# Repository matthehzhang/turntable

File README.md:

# turntable
im building a vinyl record player from scratch

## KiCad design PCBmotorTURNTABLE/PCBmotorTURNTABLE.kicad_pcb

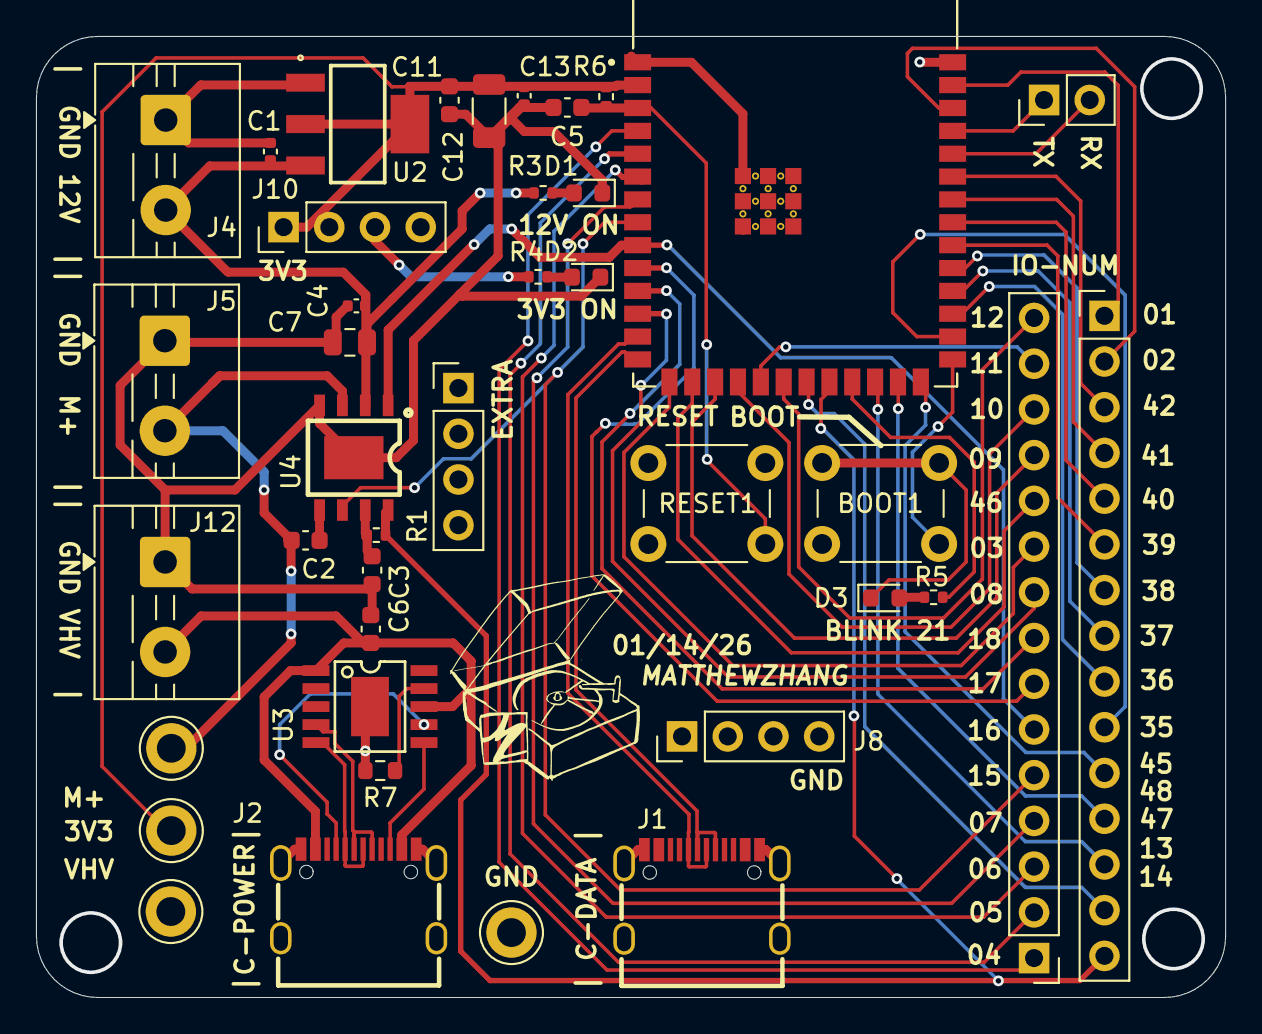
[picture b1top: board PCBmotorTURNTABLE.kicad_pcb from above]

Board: 2 copper layers, 66.1 x 53.4 mm, 40 parts (0 on the bottom side), 53 nets.

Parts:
3V3: TestPoint; TestPoint_Keystone_5010-5014_Multipurpose
BOOT1: SW_Push; SW_PUSH_6mm
C1: 100nf; C_0402_1005Metric
C2: 47nF; C_0603_1608Metric
C3, C6: 1uF; C_0603_1608Metric
C4: 0.1uF; C_0402_1005Metric
C5, C11: 10u; C_0603_1608Metric
C7: 10uF; C_0805_2012Metric
C12: 22u; C_1206_3216Metric
C13: 100n; C_0402_1005Metric
D1: RED; D_0603_1608Metric
D2, D3: GREEN; D_0603_1608Metric
EXTRA: Conn_01x04_Pin; PinHeader_1x04_P2.54mm_Vertical
GND: GND; TestPoint_Keystone_5010-5014_Multipurpose
J1, J2: USB_C_Receptacle_USB2.0_16P; USB-C_SMD-TYPE-C-31-M-12_1
J3, J6: Conn_01x15_Pin; PinHeader_1x15_P2.54mm_Vertical
J4, J5, J12: Screw_Terminal_01x02; TerminalBlock_MaiXu_MX126-5.0-02P_1x02_P5.00mm
J8, J10: Conn_01x04_Pin; PinHeader_1x04_P2.54mm_Vertical
J11: Conn_01x02_Pin; PinHeader_1x02_P2.54mm_Vertical
M+: M+; TestPoint_Keystone_5010-5014_Multipurpose
R1: 27K; R_0402_1005Metric
R3: 10k; R_0402_1005Metric
R4, R5: 1.2K; R_0402_1005Metric
R6: 10K; R_0402_1005Metric
R7: 24K; R_0603_1608Metric
RESET1: SW_Push; SW_PUSH_6mm
T2: VHV; TestPoint_Keystone_5010-5014_Multipurpose
U1: ESP32-S3-WROOM-1-N8; XCVR_ESP32-S3-WROOM-1-N8
U2: LD1117S33TR; LD11
U3: ch224a
U4: MP8040

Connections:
+3V3: 3V3.1, C11.1, C12.1, C13.1, J10.1, J10.2, J10.3, J10.4, R4.1, R6.1, U1.2 (3V3), U2.2 (OUT), U2.4 (OUT)
+12V: C1.1, C4.1, C7.1, J4.2, R3.1, U2.3 (IN), U4.2 (SP)
/M+: C2.2, J5.2, M+.1, U4.3 (SW)
/VHV: C6.1, J2.A4B9, J2.B4A9, J12.2, T2.1, U3.1 (VHV), U3.8 (VBUS)
D+: J1.A6 (D+), J1.B6 (D+), U1.14 (IO20)
D-: J1.A7 (D-), J1.B7 (D-), U1.13 (IO19)
DD+: J2.A6 (D+), J2.B6 (D+), U3.4 (DP)
DD-: J2.A7 (D-), J2.B7 (D-), U3.5 (DM)
ENABLE: C5.1, R6.2, RESET1.2, U1.3 (EN)
GND: BOOT1.1, C1.2, C3.2, C4.2, C5.2, C6.2, C7.2, C11.2, C12.2, C13.2, D1.1 (K), D2.1 (K), D3.1 (K), GND.1, J1.1, J1.4, J1.B1A12, J2.1, J2.4, J2.A1B12, J2.B1A12, J4.1, J5.1, J8.1, J8.2, J8.3, J8.4, J12.1, R7.1, RESET1.1, U1.1 (GND), U1.40 (GND), U1.41_1 (GND), U1.41_2 (GND), U1.41_3 (GND), U1.41_4 (GND), U1.41_5 (GND), U1.41_6 (GND), U1.41_7 (GND), U1.41_8 (GND), U1.41_9 (GND), U2.1 (GND), U3.11 (GND), U4.4 (GND), U4.9 (EP)
GPIO0: BOOT1.2, U1.27 (IO0)
GPIO1: J6.1, U1.39 (IO1)
GPIO2: J6.2, U1.38 (IO2)
GPIO3: J3.10, U1.15 (IO3)
GPIO4: J3.1, U1.4 (IO4)
GPIO5: J3.2, U1.5 (IO5)
GPIO6: J3.3, U1.6 (IO6)
GPIO7: J3.4, U1.7 (IO7)
GPIO8: J3.9, U1.12 (IO8)
GPIO9: J3.12, U1.17 (IO9)
GPIO10: J3.13, U1.18 (IO10)
GPIO11: J3.14, U1.19 (IO11)
GPIO12: J3.15, U1.20 (IO12)
GPIO13: J6.14, U1.21 (IO13)
GPIO14: J6.15, R1.1, U1.22 (IO14), U4.8 (FLT)
GPIO15: J3.5, U1.8 (IO15), U4.6 (SHDN)
GPIO16: J3.6, U1.9 (IO16), U4.1 (PWM)
GPIO17: J3.7, U1.10 (IO17)
GPIO18: J3.8, U1.11 (IO18)
GPIO21: R5.1, U1.23 (IO21)
GPIO35: J6.10, U1.28 (IO35)
GPIO36: J6.9, U1.29 (IO36)
GPIO37: J6.8, U1.30 (IO37)
GPIO38: J6.7, U1.31 (IO38)
GPIO39: J6.6, U1.32 (IO39)
GPIO40: J6.5, U1.33 (IO40)
GPIO41: J6.4, U1.34 (IO41)
GPIO42: J6.3, U1.35 (IO42)
GPIO45: J6.11, U1.26 (IO45)
GPIO46: J3.11, U1.16 (IO46)
GPIO47: J6.13, U1.24 (IO47)
GPIO48: J6.12, U1.25 (IO48)
unnamed: D1.2 (A), R3.2
unnamed: D2.2 (A), R4.2
unnamed: D3.2 (A), R5.2
unnamed: J2.A5 (CC1), U3.7 (CC1)
unnamed: J2.B5 (CC2), U3.6 (CC2)
unnamed: EXTRA.1, EXTRA.2, EXTRA.3, EXTRA.4
unnamed: R7.2, U3.9 (CFG1)
unnamed: C2.1, U4.5 (BS)
unnamed: C3.1, R1.2, U4.7 (DRV)
RX: J11.2, U1.36 (RXD0)
TX: J11.1, U1.37 (TXD0)

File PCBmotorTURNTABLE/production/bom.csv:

Designator,Footprint,Quantity,Value,LCSC Part #
3V3,TestPoint_Keystone_5010-5014_Multipurpose,1,TestPoint,
"BOOT1, RESET1",SW_PUSH_6mm,2,SW_Push,
C1,0402,1,100nf,
"C11, C5",0603,2,10u,
C12,1206,1,22u,
C13,0402,1,100n,
C2,0603,1,47nF,
"C3, C6",0603,2,1uF,
C4,0402,1,0.1uF,
C7,0805,1,10uF,
D1,0603,1,RED,
"D2, D3",0603,2,GREEN,
"EXTRA, J10, J8",PinHeader_1x04_P2.54mm_Vertical,3,Conn_01x04_Pin,
GND,TestPoint_Keystone_5010-5014_Multipurpose,1,GND,
"J1, J2",USB-C_SMD-TYPE-C-31-M-12_1,2,USB_C_Receptacle_USB2.0_16P,
J11,PinHeader_1x02_P2.54mm_Vertical,1,Conn_01x02_Pin,
"J12, J4, J5",TerminalBlock_MaiXu_MX126-5.0-02P_1x02_P5.00mm,3,Screw_Terminal_01x02,
"J3, J6",PinHeader_1x15_P2.54mm_Vertical,2,Conn_01x15_Pin,
M+,TestPoint_Keystone_5010-5014_Multipurpose,1,M+,
R1,0402,1,27K,
"R3, R6",0402,2,10k,
"R4, R5",0402,2,1.2K,
R7,0603,1,24K,
T2,TestPoint_Keystone_5010-5014_Multipurpose,1,VHV,
U1,XCVR_ESP32-S3-WROOM-1-N8,1,ESP32-S3-WROOM-1-N8,
U2,LD11,1,LD1117S33TR,
U3,ch224a,1,~,
U4,MP8040,1,MP8040,

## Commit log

2025-12-19 kicad files created
2025-12-25 started schematic
2025-12-25 continued schematic work
2025-12-27 finishing up basic esp32s3 hardware
2025-12-28 usb c 12v rail wip
2025-12-28 12 -> 3.3 progress
2025-12-28 12v -> 3.3v prog
2026-01-05 schematic near finish
2026-01-08 schematic finished
2026-01-12 motor pcb update
    ddd
2026-01-12 motor pcb update 3
2026-02-21 reformat
2026-03-30 firmware and cad work
2026-04-03 hall effect firmware test
2026-05-05 pcb->buckedit
